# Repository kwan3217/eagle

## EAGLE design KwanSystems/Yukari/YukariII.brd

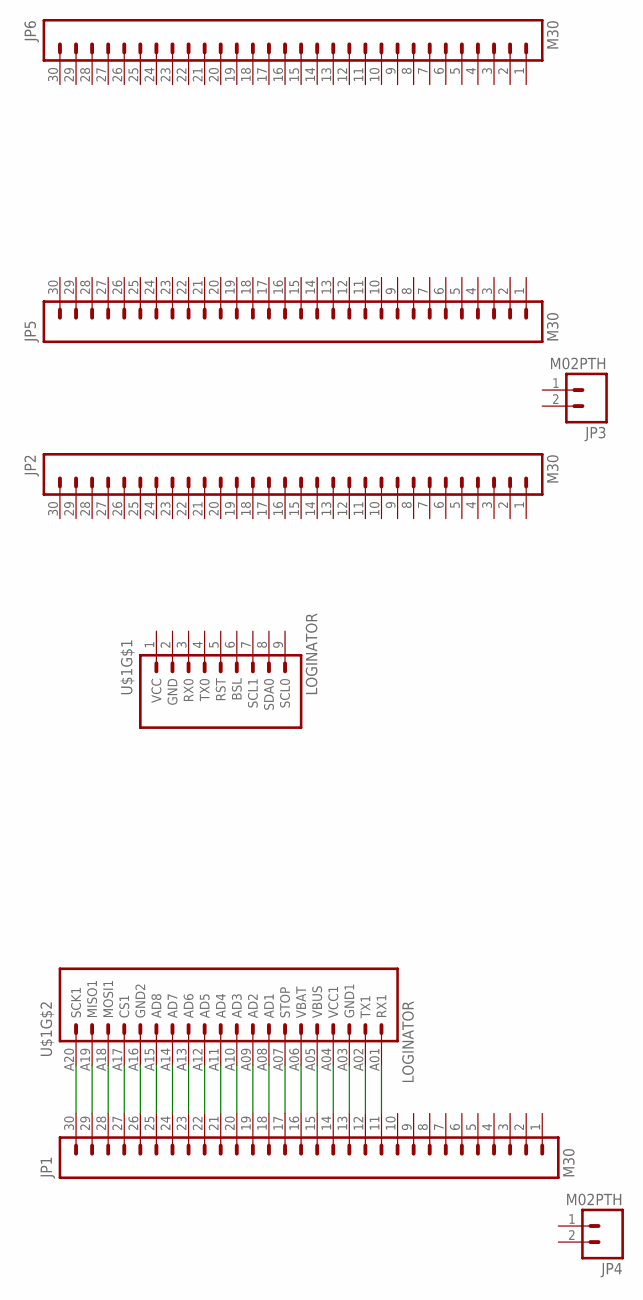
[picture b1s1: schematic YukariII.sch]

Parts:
JP1, JP2, JP5, JP6: M30; 1X30
JP3, JP4: M02PTH; 1X02
U$1: LOGINATOR

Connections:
GND: U$1.2 (GND)
unnamed: JP1.11, U$1.A01 (RX1)
unnamed: JP1.12, U$1.A02 (TX1)
unnamed: JP1.13, U$1.A03 (GND1)
unnamed: JP1.14, U$1.A04 (VCC1)
unnamed: JP1.15, U$1.A05 (VBUS)
unnamed: JP1.16, U$1.A06 (VBAT)
unnamed: JP1.17, U$1.A07 (STOP)
unnamed: JP1.18, U$1.A08 (AD1)
unnamed: JP1.19, U$1.A09 (AD2)
unnamed: JP1.20, U$1.A10 (AD3)
unnamed: JP1.21, U$1.A11 (AD4)
unnamed: JP1.22, U$1.A12 (AD5)
unnamed: JP1.23, U$1.A13 (AD6)
unnamed: JP1.24, U$1.A14 (AD7)
unnamed: JP1.25, U$1.A15 (AD8)
unnamed: JP1.26, U$1.A16 (GND2)
unnamed: JP1.27, U$1.A17 (CS1)
unnamed: JP1.28, U$1.A18 (MOSI1)
unnamed: JP1.29, U$1.A19 (MISO1)
unnamed: JP1.30, U$1.A20 (SCK1)
VCC: U$1.1 (VCC)

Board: 2 copper layers, 8 parts (0 on the bottom side), 20 nets, no tracks yet.

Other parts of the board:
U$4: AXES

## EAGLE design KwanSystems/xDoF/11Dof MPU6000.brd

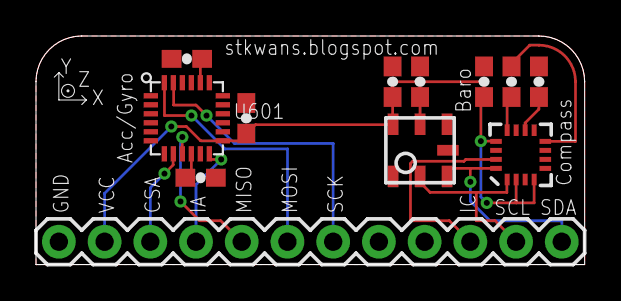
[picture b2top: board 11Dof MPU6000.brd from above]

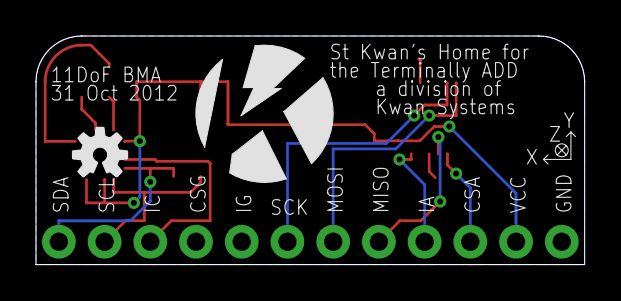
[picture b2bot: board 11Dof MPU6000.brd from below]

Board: 2 copper layers, 30.5 x 12.7 mm, 14 parts (2 on the bottom side), 15 nets.

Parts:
C102, C103, C610, C613, C802: 100nF; 0603-CAP
C620: 2.2nF; 0603-CAP
C808: 220nF; 0603-CAP
C810: 4.7uF; 0603-CAP
J401: 1X12
U101: BMP180
U601: MPU6000; MPU60X0
U801: 5883; 16LPCC
U$1: KWAN_CIRCLE
U$2: OSHW-LOGOS; OSHW-LOGO-S

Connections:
AI: J401.9, U601.12
CI: J401.3, U801.15
CSA: J401.10, U601.8
GND: C102.2, C103.2, C610.2, C613.1, C620.1, C802.2, C810.2, J401.12, U101.7, U601.1, U601.11, U601.18, U801.9, U801.11
MISO: J401.8, U601.9
MOSI: J401.7, U601.24
unnamed: C610.1, U601.10
unnamed: C620.2, U601.20
unnamed: C808.1, U801.8
unnamed: C808.2, U801.12
unnamed: C810.1, U801.10
SCK: J401.6, U601.23
SCL: J401.2, U101.5, U801.1
SDA: J401.1, U101.6, U801.16
VCC: C102.1, C103.1, C613.2, C802.1, J401.11, U101.2, U101.3, U601.13, U801.2, U801.4, U801.13

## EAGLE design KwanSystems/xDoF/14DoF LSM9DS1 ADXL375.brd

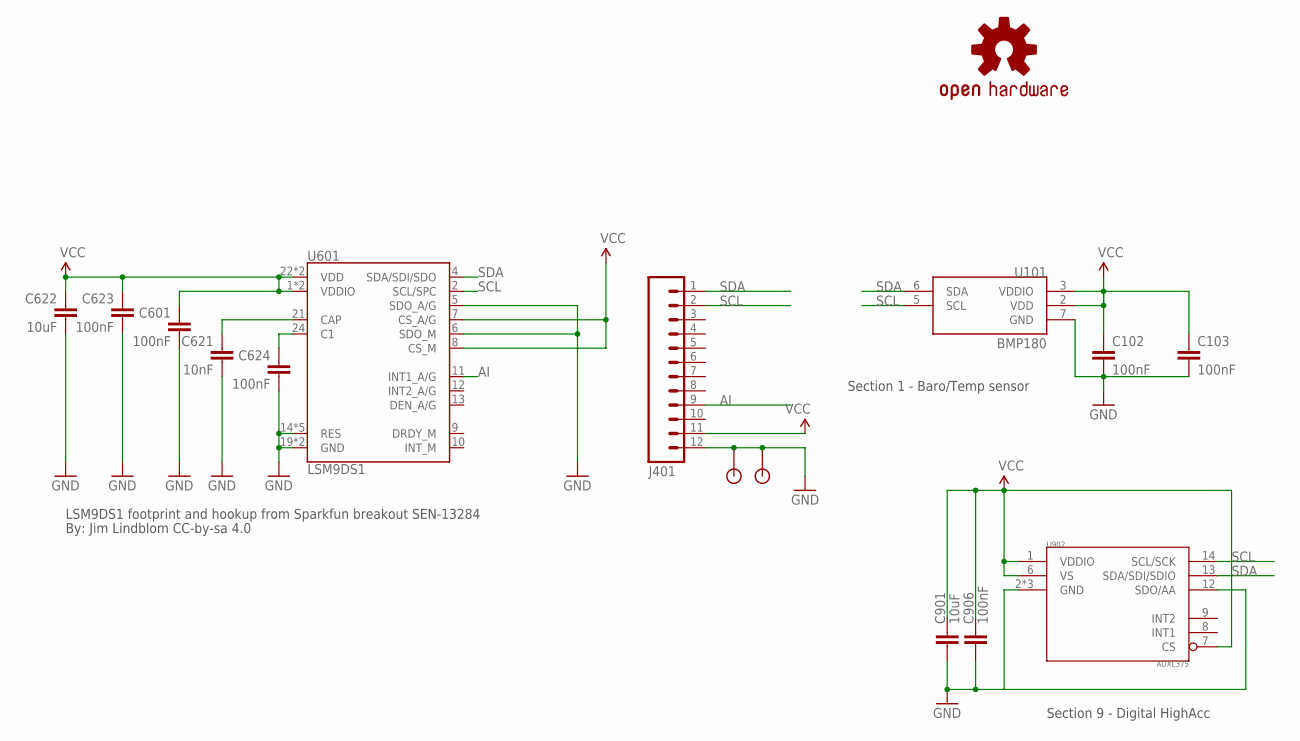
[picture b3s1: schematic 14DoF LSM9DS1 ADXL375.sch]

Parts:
C102, C103, C906: 100nF; 0603-CAP; DIGIKEY 445-1317-2-ND
C601, C623, C624: 100nF; 0603-CAP
C621: 10nF; 0603-CAP
C622: 10uF; 0603-CAP
C901: 10uF; 0603-CAP; DIGIKEY 445-7486-1-ND
J401: M12PTH; 1X12; DIGIKEY $NOPART
U101: BMP180; DIGIKEY 828-1027-1-ND
U601: LSM9DS1; LGA24-8X4
U902: ADXL375
U$2: OSHW-LOGOS; OSHW-LOGO-S; DIGIKEY $NOPART
U$4, U$5: STANDOFF

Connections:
AI: J401.9, U601.11 (INT1_A/G)
C1: C624.1, U601.24 (C1)
CAP: C621.1, U601.21 (CAP)
GND: C102.2, C103.2, C601.2, C621.2, C622.2, C623.2, C624.2, C901.2, C906.2, J401.12, U101.7 (GND), U601.5 (SDO_A/G), U601.6 (SDO_M), U601.14 (RES), U601.15 (RES), U601.16 (RES), U601.17 (RES), U601.18 (RES), U601.19 (GND), U601.20 (GND), U902.2 (GND), U902.4 (GND), U902.5 (GND), U902.12 (SDO/AA), U$4.P$1, U$5.P$1
SCL: J401.2, U101.5 (SCL), U601.2 (SCL/SPC), U902.14 (SCL/SCK)
SDA: J401.1, U101.6 (SDA), U601.4 (SDA/SDI/SDO), U902.13 (SDA/SDI/SDIO)
VCC: C102.1, C103.1, C601.1, C622.1, C623.1, C901.1, C906.1, J401.11, U101.2 (VDD), U101.3 (VDDIO), U601.1 (VDDIO), U601.3 (VDDIO), U601.7 (CS_A/G), U601.8 (CS_M), U601.22 (VDD), U601.23 (VDD), U902.1 (VDDIO), U902.6 (VS)

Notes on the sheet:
Section 1 - Baro/Temp sensor
Section 9 - Digital HighAcc
LSM9DS1 footprint and hookup from Sparkfun breakout SEN-13284
By: Jim Lindblom CC-by-sa 4.0

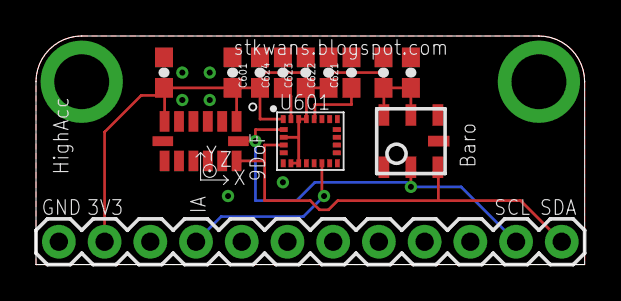
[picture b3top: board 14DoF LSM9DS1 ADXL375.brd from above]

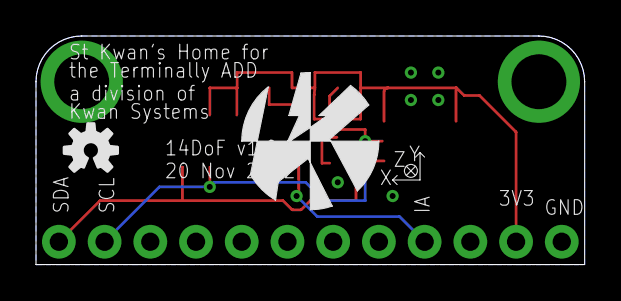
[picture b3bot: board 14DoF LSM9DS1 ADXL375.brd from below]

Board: 2 copper layers, 30.5 x 12.7 mm, 18 parts (2 on the bottom side), 7 nets.

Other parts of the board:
U$1: KWAN_ACC
U$3: AXES_SM

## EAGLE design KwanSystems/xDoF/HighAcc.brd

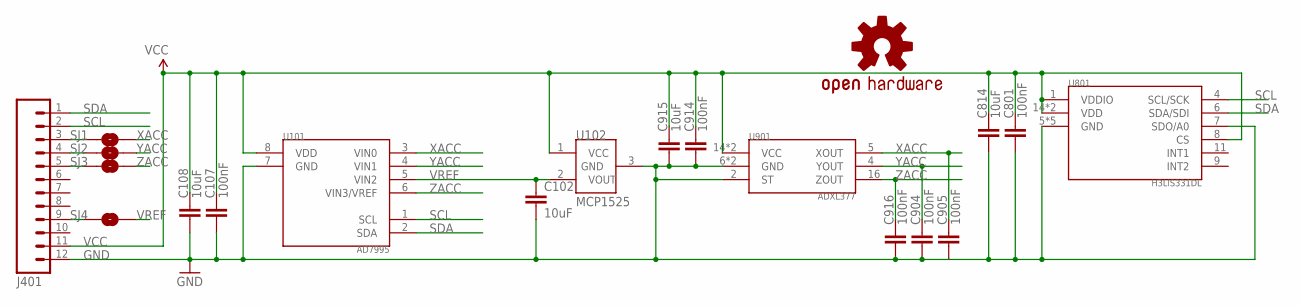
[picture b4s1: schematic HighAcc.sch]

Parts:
C102, C108, C814, C915: 10uF; 0603-CAP; DIGIKEY 445-7486-1-ND
C107, C801, C904, C905, C914, C916: 100nF; 0603-CAP; DIGIKEY 445-1316-1-ND
J401: M12PTH; 1X12; DIGIKEY $NOPART
SJ1, SJ2, SJ3, SJ4: SOLDERJUMPERNO; SJ_2S-NO; DIGIKEY $NOPART
U101: AD7995; SOT-23-8; DIGIKEY AD7995YRJZ-1500RL7CT-ND
U102: MCP1525; SOT-23-3; DIGIKEY MCP1525T-I/TTCT-ND
U801: H3LIS331DL; LLGA16; DIGIKEY $NOPART
U901: ADXL377; DIGIKEY ADXL377BCPZ-RL7CT-ND
U$2: OSHW-LOGOS; OSHW-LOGO-S; DIGIKEY $NOPART

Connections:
GND: C102.2, C107.2, C108.2, C801.2, C814.2, C904.2, C905.2, C914.2, C915.2, C916.2, J401.12, U101.7 (GND), U102.3 (GND), U801.5 (GND), U801.7 (SDO/A0), U801.10 (GND), U801.12 (GND), U801.13 (GND), U801.16 (GND), U901.2 (ST), U901.6 (GND), U901.7 (GND)
unnamed: J401.3, SJ1.1
unnamed: J401.4, SJ2.1
unnamed: J401.5, SJ3.1
unnamed: J401.9, SJ4.1
SCL: J401.2, U101.1 (SCL), U801.4 (SCL/SCK)
SDA: J401.1, U101.2 (SDA), U801.6 (SDA/SDI)
VCC: C107.1, C108.1, C801.1, C814.1, C914.1, C915.1, J401.11, U101.8 (VDD), U102.1 (VCC), U801.1 (VDDIO), U801.8 (CS), U801.14 (VDD), U801.15 (VDD), U901.14 (VCC), U901.15 (VCC)
VREF: C102.1, SJ4.2, U101.5 (VIN2), U102.2 (VOUT)
XACC: C905.1, SJ1.2, U101.3 (VIN0), U901.5 (XOUT)
YACC: C904.1, SJ2.2, U101.4 (VIN1), U901.4 (YOUT)
ZACC: C916.1, SJ3.2, U101.6 (VIN3/VREF), U901.16 (ZOUT)

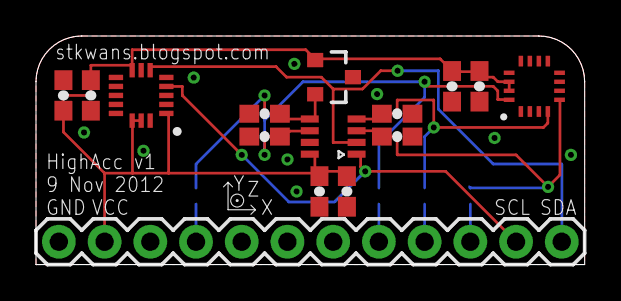
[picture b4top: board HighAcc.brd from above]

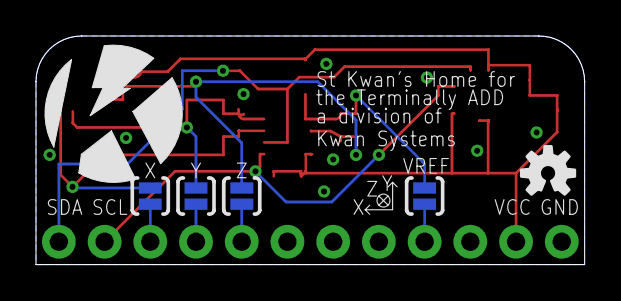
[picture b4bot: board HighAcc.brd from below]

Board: 2 copper layers, 30.5 x 12.7 mm, 22 parts (6 on the bottom side), 12 nets.

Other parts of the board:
U$1: KWAN_CIRCLE
U$4: AXES_SM

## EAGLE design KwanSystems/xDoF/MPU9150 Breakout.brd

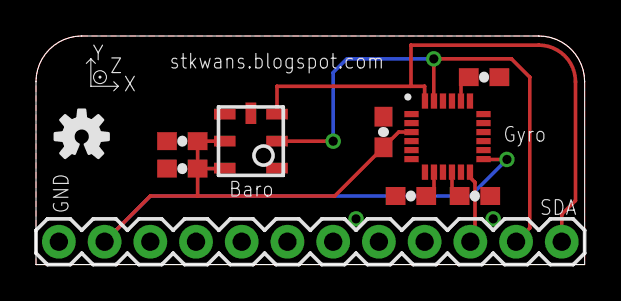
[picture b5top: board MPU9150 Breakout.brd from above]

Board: 2 copper layers, 30.5 x 12.7 mm, 11 parts (1 on the bottom side), 8 nets.

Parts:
C102, C103, C501, C502, C504: 100nF; 0603-CAP
C503: 2.2nF; 0603-CAP
J401: 1X12
U101: BMP180
U501: MPU9150; LLGA24
U$1: KWAN_CIRCLE
U$2: OSHW-LOGOS; OSHW-LOGO-S

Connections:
CI: J401.3, U501.12
GND: C102.2, C103.2, C501.1, C502.1, C503.2, C504.1, J401.12, U101.7, U501.1, U501.9, U501.15, U501.17, U501.18
unnamed: C503.1, U501.20
unnamed: C501.2, U501.10
unnamed: C504.2, U501.8
SCL: J401.2, U101.5, U501.23
SDA: J401.1, U101.6, U501.24
VCC: C102.1, C103.1, C502.2, J401.11, U101.2, U101.3, U501.3, U501.13

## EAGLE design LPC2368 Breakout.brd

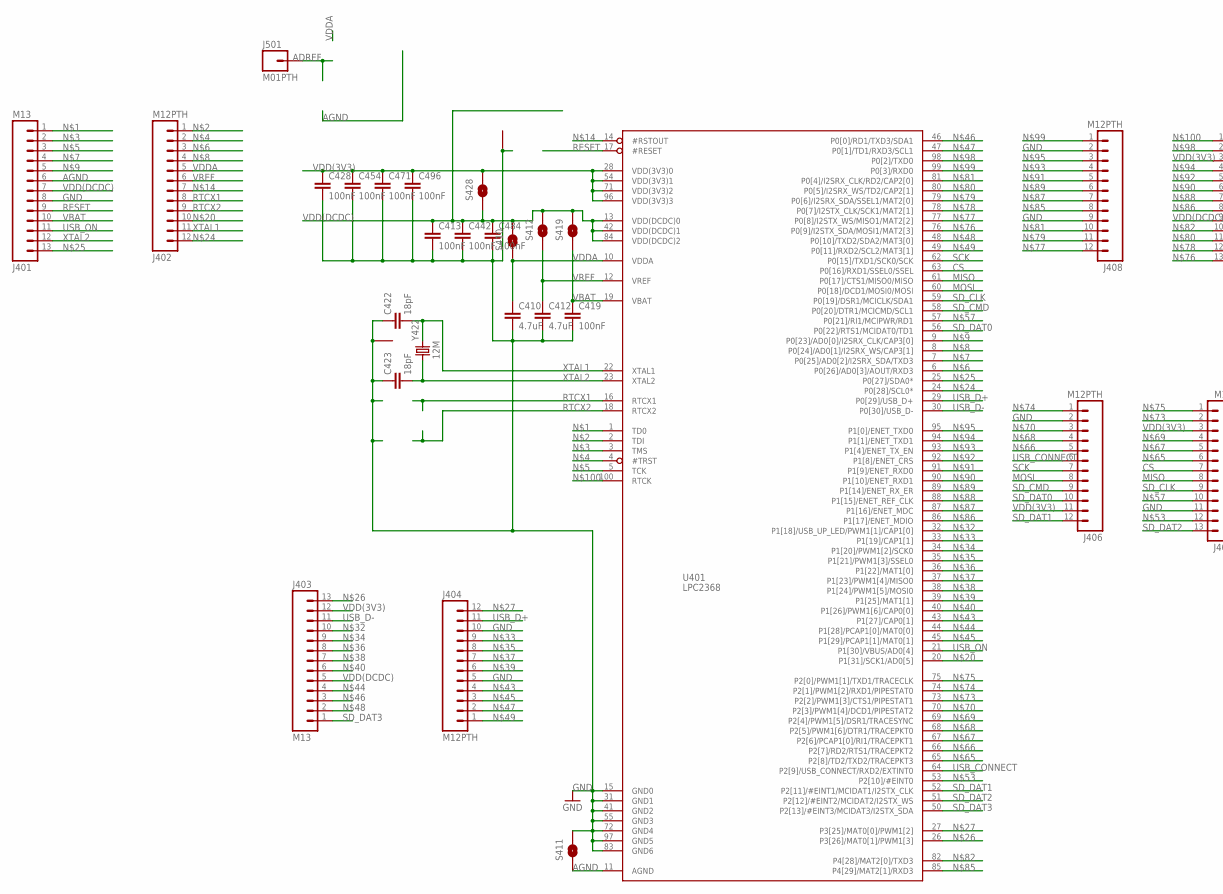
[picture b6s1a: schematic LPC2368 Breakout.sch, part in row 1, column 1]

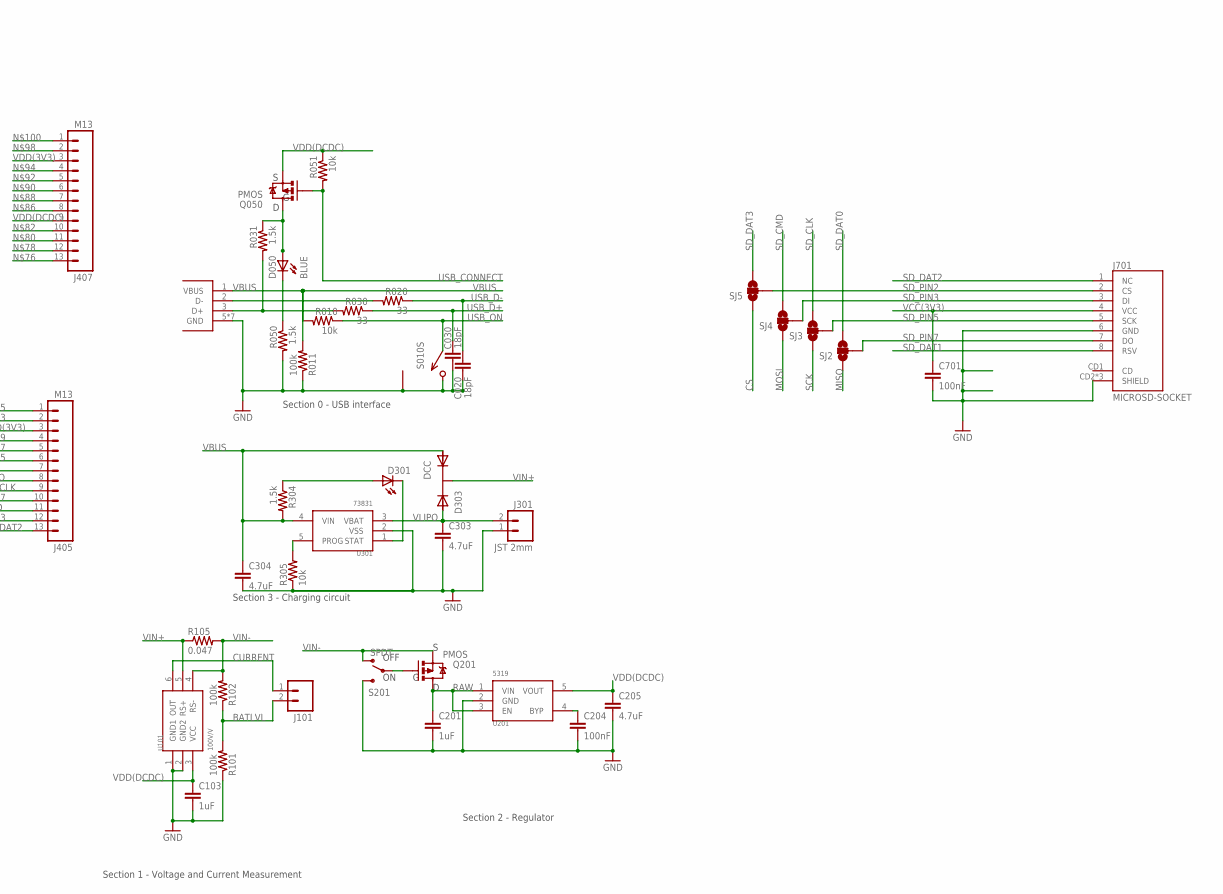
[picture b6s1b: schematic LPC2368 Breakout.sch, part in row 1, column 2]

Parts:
C020, C030, C422, C423: 18pF; 0402-CAP; DIGIKEY 445-1238-1-ND
C103, C201: 1uF; 0402-CAP; DIGIKEY 445-1415-1-ND
C204, C413, C419, C428, C442, C454, C471, C484, C496, C701: 100nF; 0402-CAP; DIGIKEY 445-1268-1-ND
C205, C303, C304, C410, C412: 4.7uF; 0402-CAP; DIGIKEY 445-7395-1-ND
D050: BLUE; LED-0603; DIGIKEY 754-1434-1-ND
D301: YELLOW; LED-0603; DIGIKEY 754-1354-1-ND
D303: DCC; SOT-23-3; DIGIKEY 568-6500-1-ND
J001: USB_MICROB_JST; UB-MC5BR3-SD204-4S; DIGIKEY 455-2562-1-ND
J101: M02PTH; 1X02; DIGIKEY $NOPART
J301: JST 2mm; JST-2-SMD; DIGIKEY 455-1749-1-ND
J401, J403, J405, J407: M13; 1X13; DIGIKEY $NOPART
J402, J404, J406, J408: M12PTH; 1X12; DIGIKEY $NOPART
J501: M01PTH; 1X01; DIGIKEY $NOPART
J701: MICROSD-SOCKET; MICROSD-SOCKET-PP; DIGIKEY 101-00581-59-1-ND
Q050, Q201: PMOS; SOT23-3; DIGIKEY NTR1P02T1GOSCT-ND
R010, R051, R305: 10k; 0402-RES; DIGIKEY P10.0KLCT-ND
R011, R101, R102: 100k; 0402-RES; DIGIKEY P100KLCT-ND
R020, R030: 33; 0402-RES; DIGIKEY P33.0LCT-ND
R031, R050, R304: 1.5k; 0402-RES; DIGIKEY P1.50KLCT-ND
R105: 0.047; 0402-RES; DIGIKEY P.047ATCT-ND
S010, S417: SPST; B3U-1100P; DIGIKEY SW1021CT-ND
S201: SPDT; AYZ0202; DIGIKEY 401-2013-1-ND
S410, S411, S412, S419, S428: SOLDERJUMPERNO; SJ_2S-NO; DIGIKEY $NOPART
SJ2, SJ3, SJ4, SJ5: SOLDERJUMPER_2WAYS; SJ_3; DIGIKEY $NOPART
U101: 100V/V; SOT-23-6; DIGIKEY MAX4173HEUT+TCT-ND
U201: 5319; SOT-23-5; DIGIKEY 576-1910-1-ND
U301: 73831; SOT-23-5; DIGIKEY MCP73831T-2ACI/OTCT-ND
U401: LPC2368; LQFP100; DIGIKEY 568-3997-ND
Y422: 12M; CRYSTAL_SMD; DIGIKEY 887-1316-1-ND

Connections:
ADREF: J501.1
AGND: J401.6, S411.1, U401.11 (AGND)
BATLVL: J101.2, R101.2, R102.1
CONN_D+: J001.3 (D+), R030.2, R031.2
CONN_D-: J001.2 (D-), R020.2
CS: J405.7, SJ5.1, U401.63 (P0[16]/RXD1/SSEL0/SSEL)
CURRENT: J101.1, U101.6 (OUT)
C_STAT: D301.C, U301.1 (STAT)
DR_STAT: D301.A, R304.1
GND: C020.2, C030.2, C103.2, C201.2, C204.2, C205.2, C303.2, C304.2, C410.2, C412.2, C413.2, C419.2, C422.1, C423.1, C428.2, C442.2, C454.2, C471.2, C484.2, C496.2, C701.2, J001.5 (GND), J001.P$6 (GND), J001.P$7 (GND), J001.P$8 (GND), J001.P$9 (GND), J001.P$10 (GND), J001.P$11 (GND), J301.1, J401.8, J404.5, J404.10, J405.11, J406.2, J408.2, J408.9, J701.6 (GND), J701.CD2 (SHIELD), J701.GND1 (SHIELD), J701.GND3 (SHIELD), R011.1, R050.2, R101.1, R305.1, S010.P$2 (2), S010.P$3 (1), S201.3 (S), S411.2, S417.P$3 (1), U101.1 (GND1), U101.2 (GND2), U201.2 (GND), U301.2 (VSS), U401.15 (GND0), U401.31 (GND1), U401.41 (GND2), U401.55 (GND3), U401.72 (GND4), U401.83 (GND6), U401.97 (GND5), Y422.2 (1), Y422.4 (1)
MISO: J405.8, SJ2.1, U401.61 (P0[17]/CTS1/MISO0/MISO)
MOSI: J406.8, SJ4.1, U401.60 (P0[18]/DCD1/MOSI0/MOSI)
unnamed: J401.1, U401.1 (TD0)
unnamed: J402.1, U401.2 (TDI)
unnamed: J401.2, U401.3 (TMS)
unnamed: J402.2, U401.4 (#TRST)
unnamed: J401.3, U401.5 (TCK)
unnamed: J402.3, U401.6 (P0[26]/AD0[3]/AOUT/RXD3)
unnamed: J401.4, U401.7 (P0[25]/AD0[2]/I2SRX_SDA/TXD3)
unnamed: J402.4, U401.8 (P0[24]/AD0[1]/I2SRX_WS/CAP3[1])
unnamed: J401.5, U401.9 (P0[23]/AD0[0]/I2SRX_CLK/CAP3[0])
unnamed: R305.2, U301.5 (PROG)
unnamed: J402.7, U401.14 (#RSTOUT)
unnamed: C204.1, U201.4 (BYP)
unnamed: D050.C, R050.1
unnamed: Q201.1 (G), S201.2
unnamed: J402.10, U401.20 (P1[31]/SCK1/AD0[5])
unnamed: J402.12, U401.24 (P0[28]/SCL0*)
unnamed: J401.13, U401.25 (P0[27]/SDA0*)
unnamed: J403.13, U401.26 (P3[26]/MAT0[1]/PWM1[3])
unnamed: J404.12, U401.27 (P3[25]/MAT0[0]/PWM1[2])
unnamed: D050.A, Q050.3 (D), R031.1
unnamed: J403.10, U401.32 (P1[18]/USB_UP_LED/PWM1[1]/CAP1[0])
unnamed: J404.9, U401.33 (P1[19]/CAP1[1])
unnamed: J403.9, U401.34 (P1[20]/PWM1[2]/SCK0)
unnamed: J404.8, U401.35 (P1[21]/PWM1[3]/SSEL0)
unnamed: J403.8, U401.36 (P1[22]/MAT1[0])
unnamed: J404.7, U401.37 (P1[23]/PWM1[4]/MISO0)
unnamed: J403.7, U401.38 (P1[24]/PWM1[5]/MOSI0)
unnamed: J404.6, U401.39 (P1[25]/MAT1[1])
unnamed: J403.6, U401.40 (P1[26]/PWM1[6]/CAP0[0])
unnamed: J404.4, U401.43 (P1[27]/CAP0[1])
unnamed: J403.4, U401.44 (P1[28]/PCAP1[0]/MAT0[0])
unnamed: J404.3, U401.45 (P1[29]/PCAP1[1]/MAT0[1])
unnamed: J403.3, U401.46 (P0[0]/RD1/TXD3/SDA1)
unnamed: J404.2, U401.47 (P0[1]/TD1/RXD3/SCL1)
unnamed: J403.2, U401.48 (P0[10]/TXD2/SDA2/MAT3[0])
unnamed: J404.1, U401.49 (P0[11]/RXD2/SCL2/MAT3[1])
unnamed: J405.12, U401.53 (P2[10]/#EINT0)
unnamed: J405.10, U401.57 (P0[21]/RI1/MCIPWR/RD1)
unnamed: J405.6, U401.65 (P2[8]/TD2/TXD2/TRACEPKT3)
unnamed: J406.5, U401.66 (P2[7]/RD2/RTS1/TRACEPKT2)
unnamed: J405.5, U401.67 (P2[6]/PCAP1[0]/RI1/TRACEPKT1)
unnamed: J406.4, U401.68 (P2[5]/PWM1[6]/DTR1/TRACEPKT0)
unnamed: J405.4, U401.69 (P2[4]/PWM1[5]/DSR1/TRACESYNC)
unnamed: J406.3, U401.70 (P2[3]/PWM1[4]/DCD1/PIPESTAT2)
unnamed: J405.2, U401.73 (P2[2]/PWM1[3]/CTS1/PIPESTAT1)
unnamed: J406.1, U401.74 (P2[1]/PWM1[2]/RXD1/PIPESTAT0)
unnamed: J405.1, U401.75 (P2[0]/PWM1[1]/TXD1/TRACECLK)
unnamed: J407.13, U401.76 (P0[9]/I2STX_SDA/MOSI1/MAT2[3])
unnamed: J408.12, U401.77 (P0[8]/I2STX_WS/MISO1/MAT2[2])
unnamed: J407.12, U401.78 (P0[7]/I2STX_CLK/SCK1/MAT2[1])
unnamed: J408.11, U401.79 (P0[6]/I2SRX_SDA/SSEL1/MAT2[0])
unnamed: J407.11, U401.80 (P0[5]/I2SRX_WS/TD2/CAP2[1])
unnamed: J408.10, U401.81 (P0[4]/I2SRX_CLK/RD2/CAP2[0])
unnamed: J407.10, U401.82 (P4[28]/MAT2[0]/TXD3)
unnamed: J408.8, U401.85 (P4[29]/MAT2[1]/RXD3)
unnamed: J407.8, U401.86 (P1[17]/ENET_MDIO)
unnamed: J408.7, U401.87 (P1[16]/ENET_MDC)
unnamed: J407.7, U401.88 (P1[15]/ENET_REF_CLK)
unnamed: J408.6, U401.89 (P1[14]/ENET_RX_ER)
unnamed: J407.6, U401.90 (P1[10]/ENET_RXD1)
unnamed: J408.5, U401.91 (P1[9]/ENET_RXD0)
unnamed: J407.5, U401.92 (P1[8]/ENET_CRS)
unnamed: J408.4, U401.93 (P1[4]/ENET_TX_EN)
unnamed: J407.4, U401.94 (P1[1]/ENET_TXD1)
unnamed: J408.3, U401.95 (P1[0]/ENET_TXD0)
unnamed: J407.2, U401.98 (P0[2]/TXD0)
unnamed: J408.1, U401.99 (P0[3]/RXD0)
unnamed: J407.1, U401.100 (RTCK)
RAW: C201.1, Q201.3 (D), U201.1 (VIN), U201.3 (EN)
RESET: J401.9, U401.17 (#RESET)
RTCX1: J402.8, U401.16 (RTCX1)
RTCX2: J402.9, U401.18 (RTCX2)
SCK: J406.7, SJ3.1, U401.62 (P0[15]/TXD1/SCK0/SCK)
SD_CLK: J405.9, SJ3.3, U401.59 (P0[19]/DSR1/MCICLK/SDA1)
SD_CMD: J406.9, SJ4.3, U401.58 (P0[20]/DTR1/MCICMD/SCL1)
SD_DAT0: J406.10, SJ2.3, U401.56 (P0[22]/RTS1/MCIDAT0/TD1)
SD_DAT1: J406.12, J701.8 (RSV), U401.52 (P2[11]/#EINT1/MCIDAT1/I2STX_CLK)
SD_DAT2: J405.13, J701.1 (NC), U401.51 (P2[12]/#EINT2/MCIDAT2/I2STX_WS)
SD_DAT3: J403.1, SJ5.3, U401.50 (P2[13]/#EINT3/MCIDAT3/I2STX_SDA)
SD_PIN2: J701.2 (CS), SJ5.2
SD_PIN3: J701.3 (DI), SJ4.2
SD_PIN5: J701.5 (SCK), SJ3.2
SD_PIN7: J701.7 (DO), SJ2.2
USB_CONNECT: J406.6, Q050.1 (G), R051.2, U401.64 (P2[9]/USB_CONNECT/RXD2/EXTINT0)
USB_D+: C030.1, J404.11, R030.1, U401.29 (P0[29]/USB_D+)
USB_D-: C020.1, J403.11, R020.1, U401.30 (P0[30]/USB_D-)
USB_ON: J401.11, R010.1, S010.P$1 (1), U401.21 (P1[30]/VBUS/AD0[4])
VBAT: C419.1, J401.10, S419.1, U401.19 (VBAT)
VBUS: C304.1, D303.1 (A1), J001.1 (VBUS), R010.2, R011.2, R304.2, U301.4 (VIN)
VCC(3V3): C701.1, J701.4 (VCC)
VDD(3V3): C428.1, C454.1, C471.1, C496.1, J403.12, J405.3, J406.11, J407.3, S428.2, U401.28 (VDD(3V3)0), U401.54 (VDD(3V3)1), U401.71 (VDD(3V3)2), U401.96 (VDD(3V3)3)
VDD(DCDC): C103.1, C205.1, C413.1, C442.1, C484.1, J401.7, J403.5, J407.9, Q050.2 (S), R051.1, S410.2, S412.2, S419.2, S428.1, U101.3 (VCC), U201.5 (VOUT), U401.13 (VDD(DCDC)0), U401.42 (VDD(DCDC)1), U401.84 (VDD(DCDC)2)
VDDA: C410.1, J402.5, S410.1, U401.10 (VDDA)
VIN+: D303.3 (K), R105.1, U101.5 (RS+)
VIN-: Q201.2 (S), R102.2, R105.2, S201.1 (O), U101.4 (RS-)
VLIPO: C303.1, D303.2 (A2), J301.2, U301.3 (VBAT)
VREF: C412.1, J402.6, S412.1, U401.12 (VREF)
XTAL1: C422.2, J402.11, U401.22 (XTAL1), Y422.3 (2)
XTAL2: C423.2, J401.12, U401.23 (XTAL2), Y422.1

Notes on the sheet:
Section 2 - Regulator
Section 3 - Charging circuit
Section 0 - USB interface
Section 1 - Voltage and Current Measurement
OFF

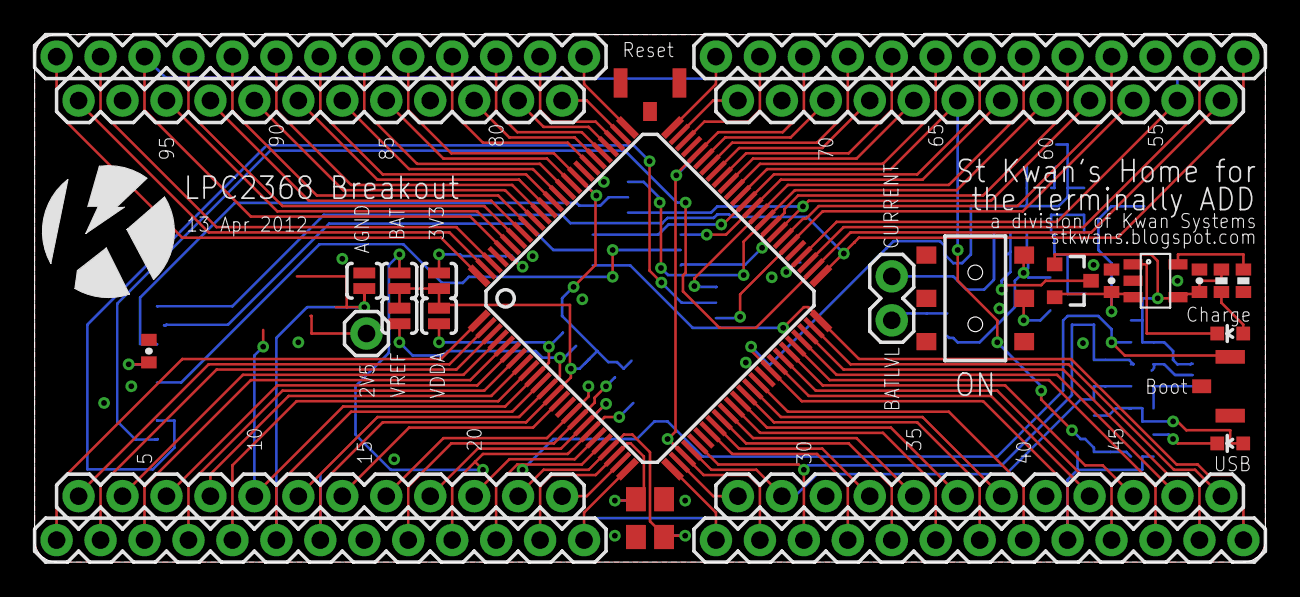
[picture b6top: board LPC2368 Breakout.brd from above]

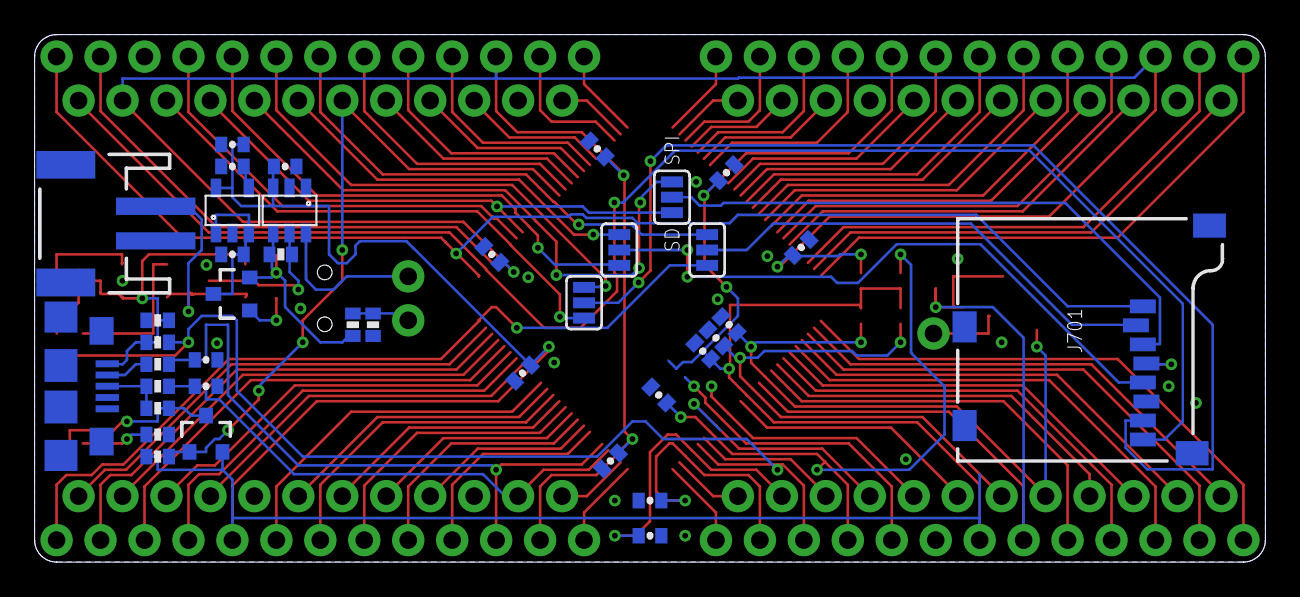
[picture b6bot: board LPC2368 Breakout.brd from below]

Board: 2 copper layers, 71.1 x 30.5 mm, 69 parts (39 on the bottom side), 110 nets.

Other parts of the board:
U$1: KWAN_CIRCLE

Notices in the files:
parts and their libraries:
SparkFun-Connectors: Licensing: CC v3.0 Share-Alike You are welcome to use this library for commercial purposes.
SparkFun-Capacitors: Licensing: Creative Commons ShareAlike 4.0 International - https://creativecommons.org/licenses/by-sa/4.0
